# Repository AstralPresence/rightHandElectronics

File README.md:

This repo contains the code on the ESP8266 and pcb designs for each unit.

Currently housing following units:

1) Switch Board Unit

2) Single switch Unit

3) Door unit

4) Safety Unit

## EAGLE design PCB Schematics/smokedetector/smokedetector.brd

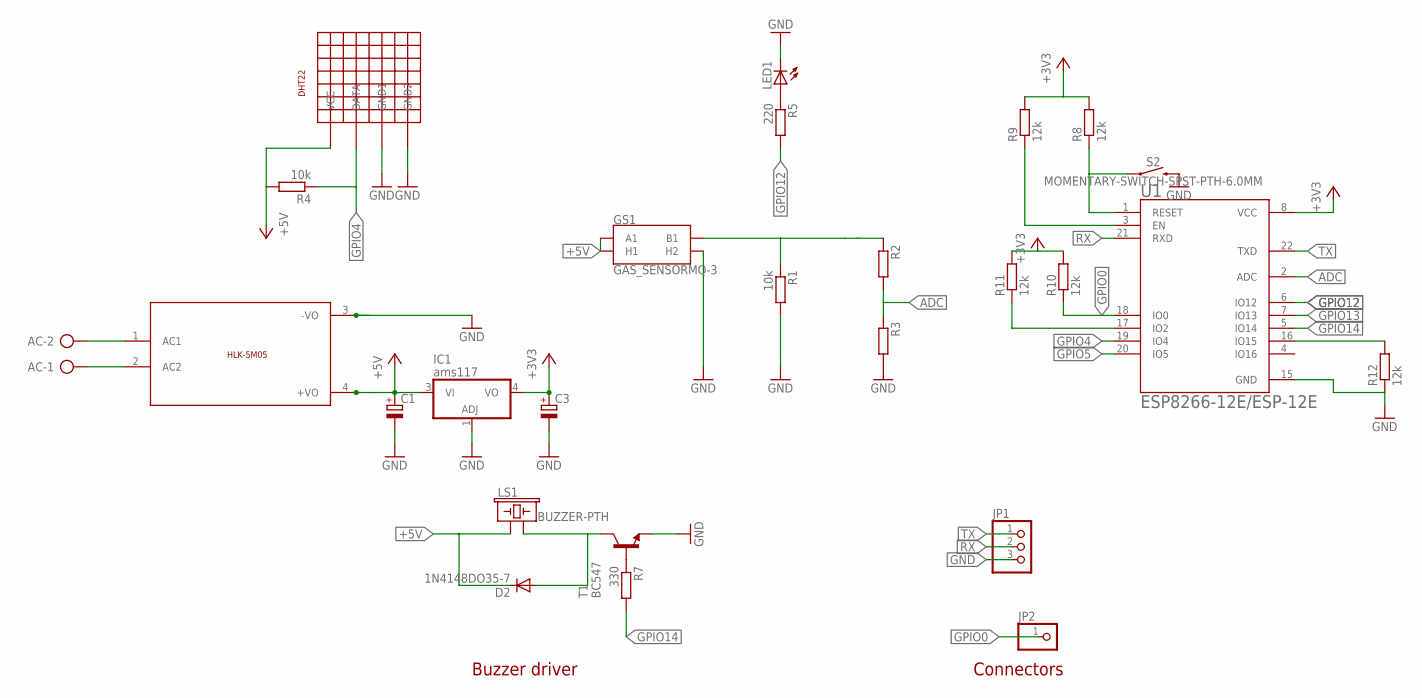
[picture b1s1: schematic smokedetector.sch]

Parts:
AC: AK500/2-H
C1, C3: CPOL-EUE2.5-6; E2,5-6
D2: 1N4148DO35-7; DO35-7
DHT22: DHT22
GS1: GAS_SENSORMQ-3; GAS_SENSOR
IC1: ams117; SOT223
JP1: PINHD-1X3CB; 1X03-CLEANBIG
JP2: PINHD-1X1CB; 1X01-CLEANBIG
LED1: LED5MM
LS1: BUZZER-PTH; BUZZER-12MM
R1, R4: 10k; 0204V
R2, R3: R-EU_0204/2V; 0204V
R5: 220; 0204V
R7: 330; 0204V
R8, R9, R10, R11, R12: 12k; 0204V
S2: MOMENTARY-SWITCH-SPST-PTH-6.0MM; TACTILE_SWITCH_PTH_6.0MM_KIT
T1: BC547; TO92
U1: ESP8266-12E/ESP-12E; XCVR_ESP8266-12E/ESP-12E
U$2: HLK-5M05

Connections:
+3V3: C3.+, IC1.4 (VO), R8.2, R9.2, R10.2, R11.2, U1.8 (VCC)
+5V: C1.+, D2.C, DHT22.P$1 (VCC), GS1.A1, GS1.HA (H1), IC1.3 (VI), LS1.+ (1), R4.2, U$2.4 (+VO)
ADC: R2.2, R3.1, U1.2 (ADC)
GND: C1.-, C3.-, DHT22.P$3 (GND1), DHT22.P$4 (GND2), GS1.HB (H2), IC1.1 (ADJ), JP1.3, LED1.K (C), R1.2, R3.2, R12.1, S2.3 (2), T1.1 (E), U1.15 (GND), U$2.3 (-VO)
GPIO0: JP2.1, R10.1, U1.18 (IO0)
GPIO4: DHT22.P$2 (DATA), R4.1, U1.19 (IO4)
GPIO5: U1.20 (IO5)
GPIO12: R5.2, U1.6 (IO12)
GPIO13: U1.7 (IO13)
GPIO14: R7.2, U1.5 (IO14)
unnamed: R7.1, T1.2 (B)
unnamed: GS1.B1, R1.1, R2.1
unnamed: R8.1, S2.1, U1.1 (RESET)
unnamed: AC.1, U$2.2 (AC2)
unnamed: AC.2, U$2.1 (AC1)
unnamed: D2.A, LS1.- (2), T1.3 (C)
unnamed: R9.1, U1.3 (EN)
unnamed: LED1.A, R5.1
unnamed: R11.1, U1.17 (IO2)
unnamed: R12.2, U1.16 (IO15)
RX: JP1.2, U1.21 (RXD)
TX: JP1.1, U1.22 (TXD)

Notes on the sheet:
Buzzer driver
Connectors

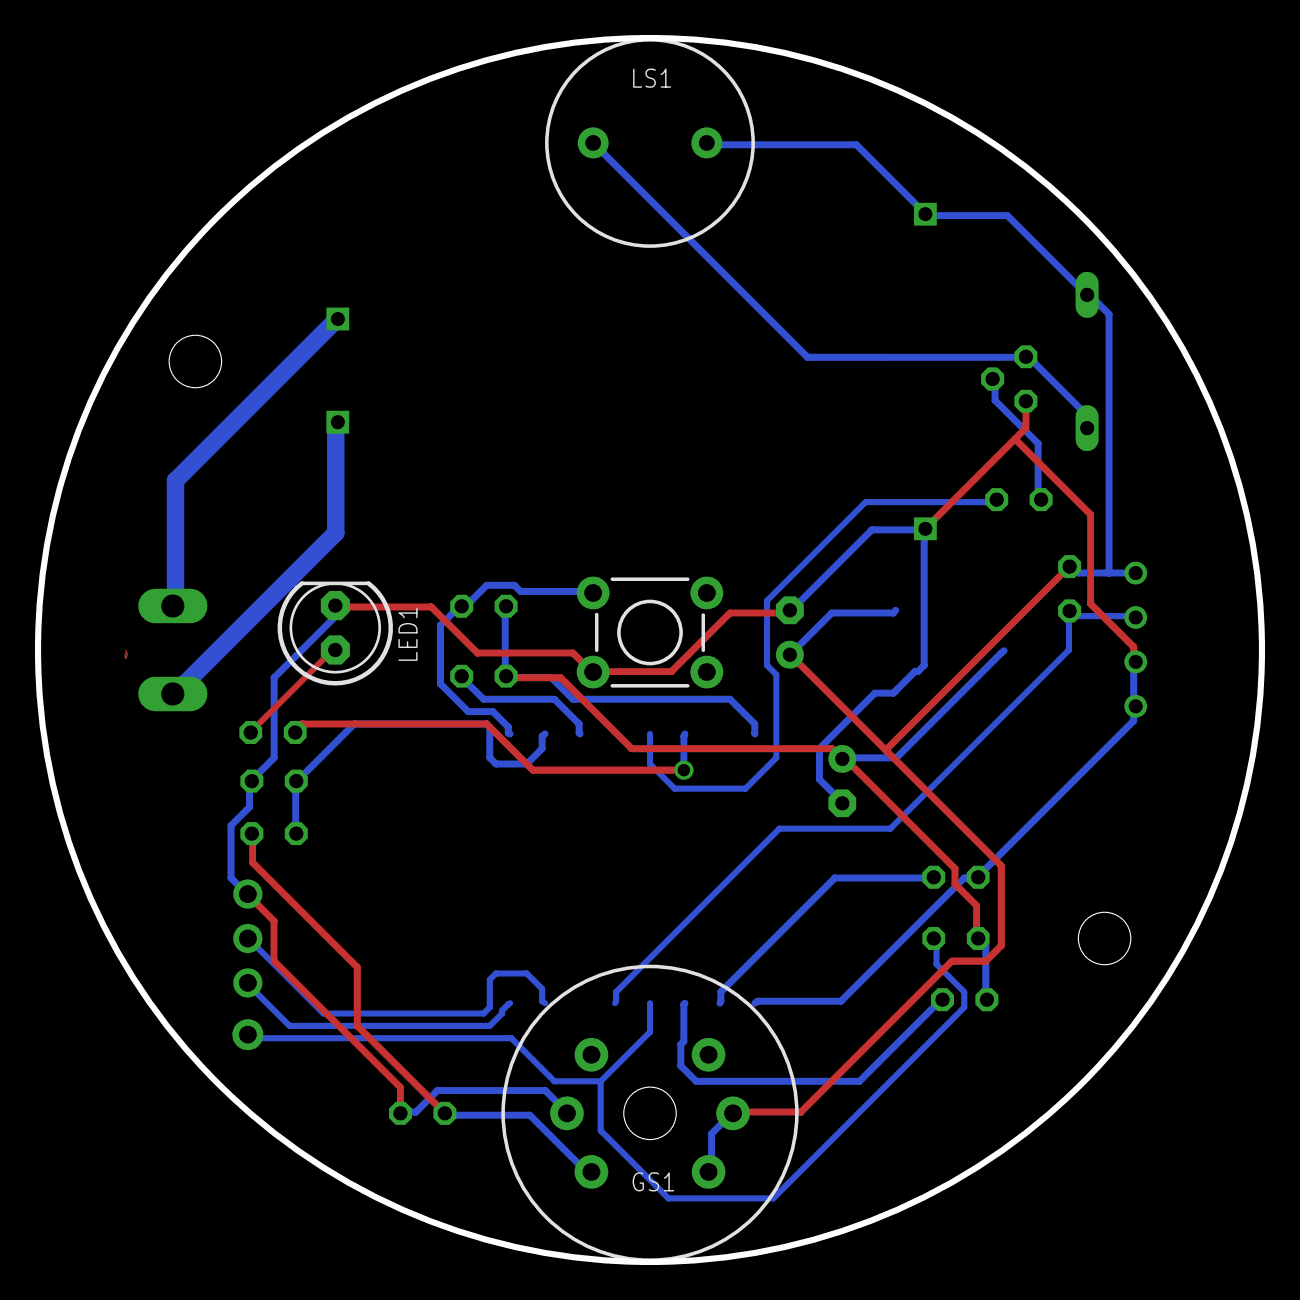
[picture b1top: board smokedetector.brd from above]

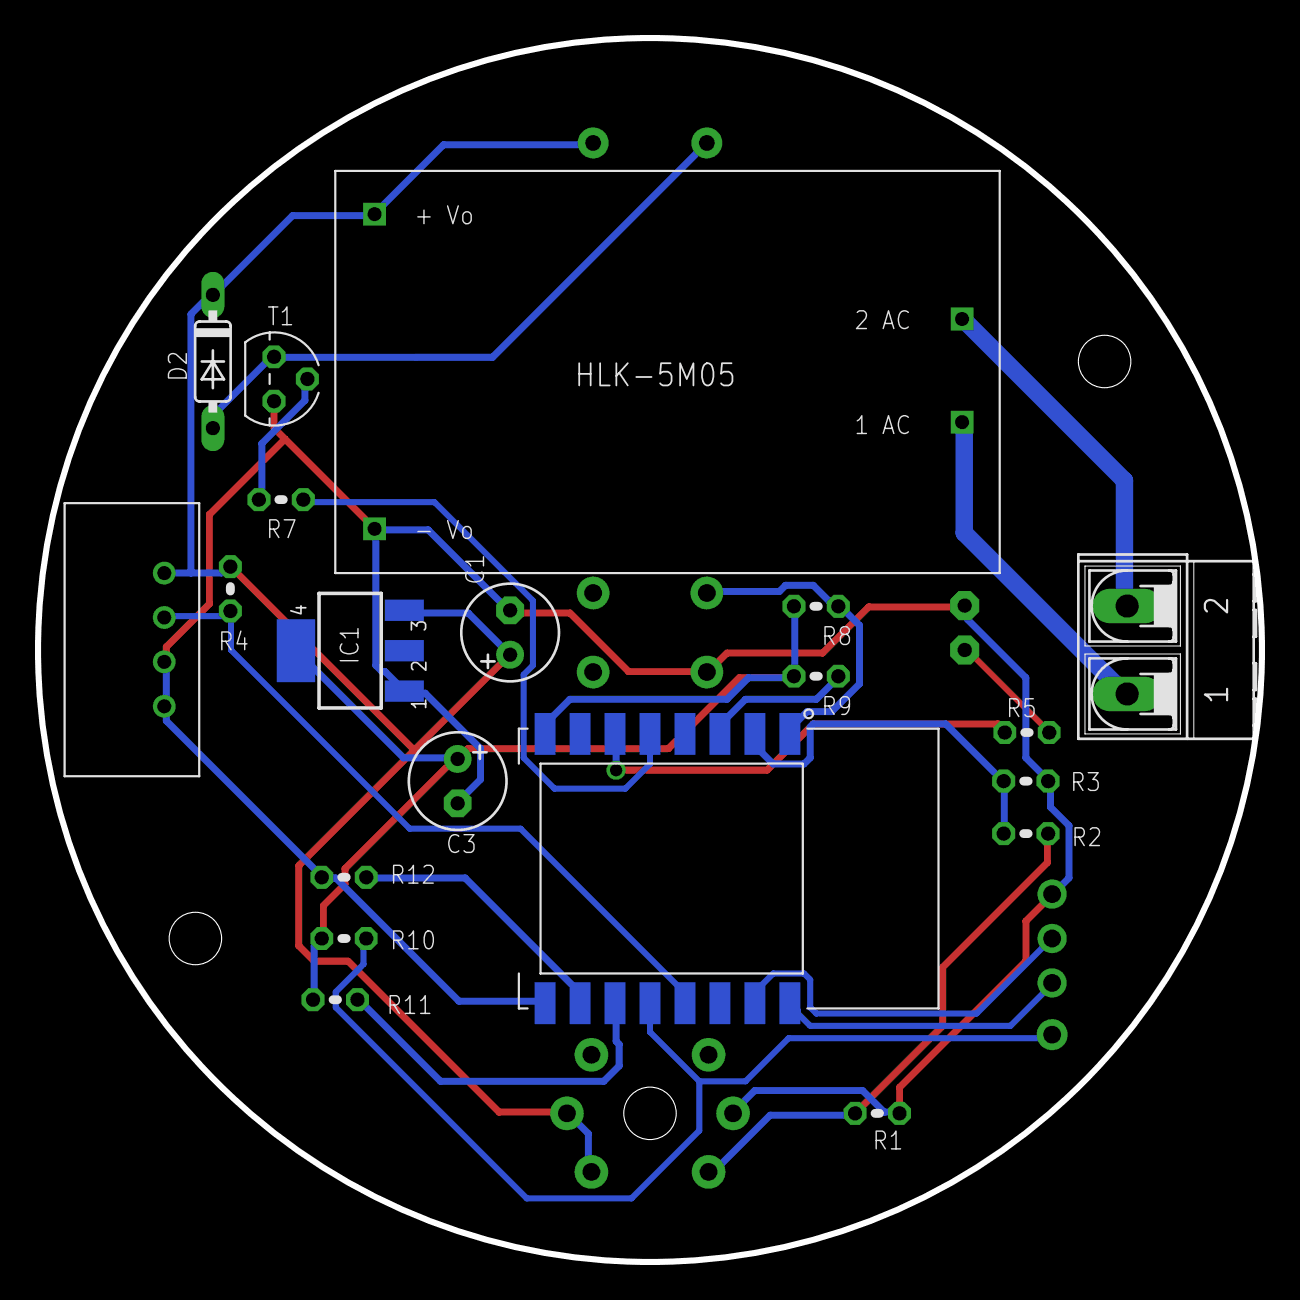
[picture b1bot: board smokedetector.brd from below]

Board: 2 copper layers, 70.0 x 70.0 mm, 26 parts (22 on the bottom side), 20 nets.

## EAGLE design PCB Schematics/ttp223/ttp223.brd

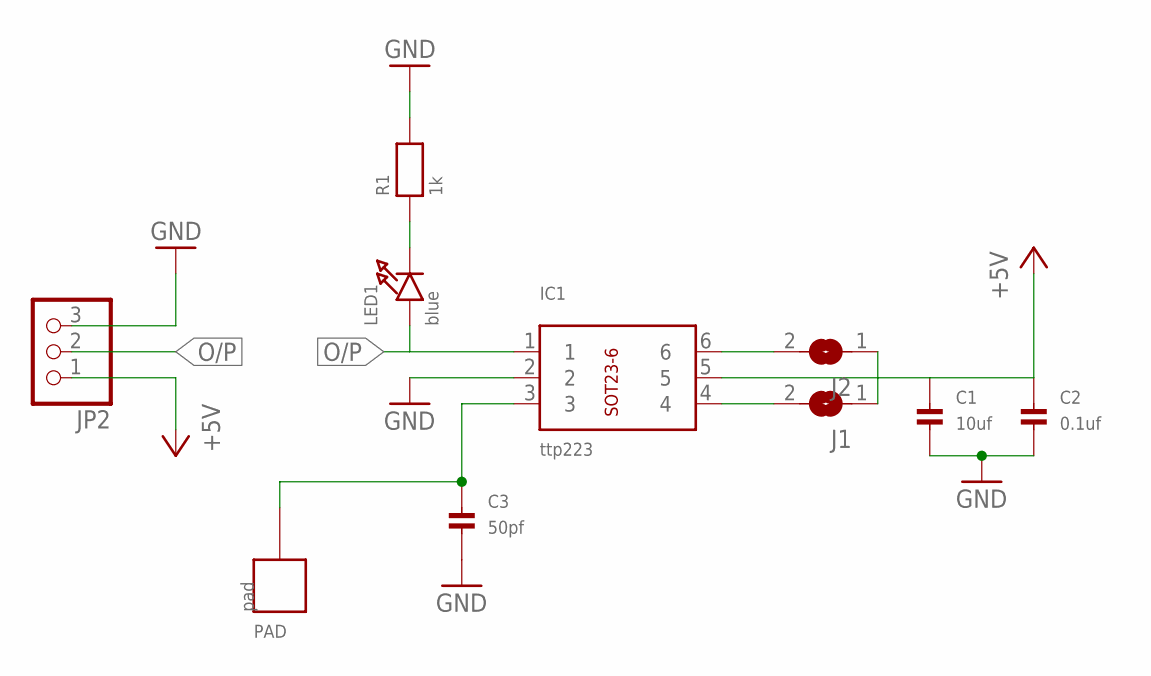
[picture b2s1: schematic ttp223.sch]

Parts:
C1: 10uf; 0805
C2: 0.1uf; 0805
C3: 50pf; 0805
IC1: ttp223; BREAKOUT_SOT23-6
J1, J2: SOLDERJUMPERREFLOW; SOLDERJUMPER_REFLOW
JP2: HEADER-1X3ROUND; 1X03_ROUND
LED1: blue; CHIPLED_0805
PAD: pad; CAP_TOUCHPAD
R1: 1k; 0805

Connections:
+5V: C1.1, C2.1, IC1.5, J1.1, J2.1, JP2.1
GND: C1.2, C2.2, C3.2, IC1.2, JP2.3, R1.2
unnamed: LED1.C, R1.1
unnamed: C3.1, IC1.3, PAD.P$1
unnamed: IC1.6, J2.2
unnamed: IC1.4, J1.2
O/P: IC1.1, JP2.2, LED1.A

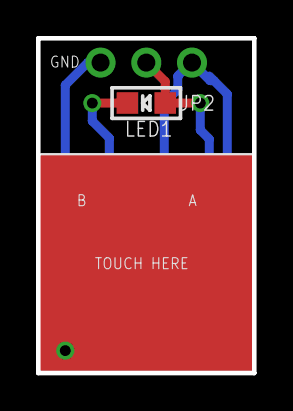
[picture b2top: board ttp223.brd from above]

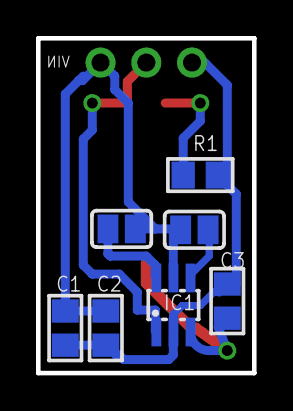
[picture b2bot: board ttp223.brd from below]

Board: 2 copper layers, 12.0 x 18.6 mm, 10 parts (7 on the bottom side), 7 nets.

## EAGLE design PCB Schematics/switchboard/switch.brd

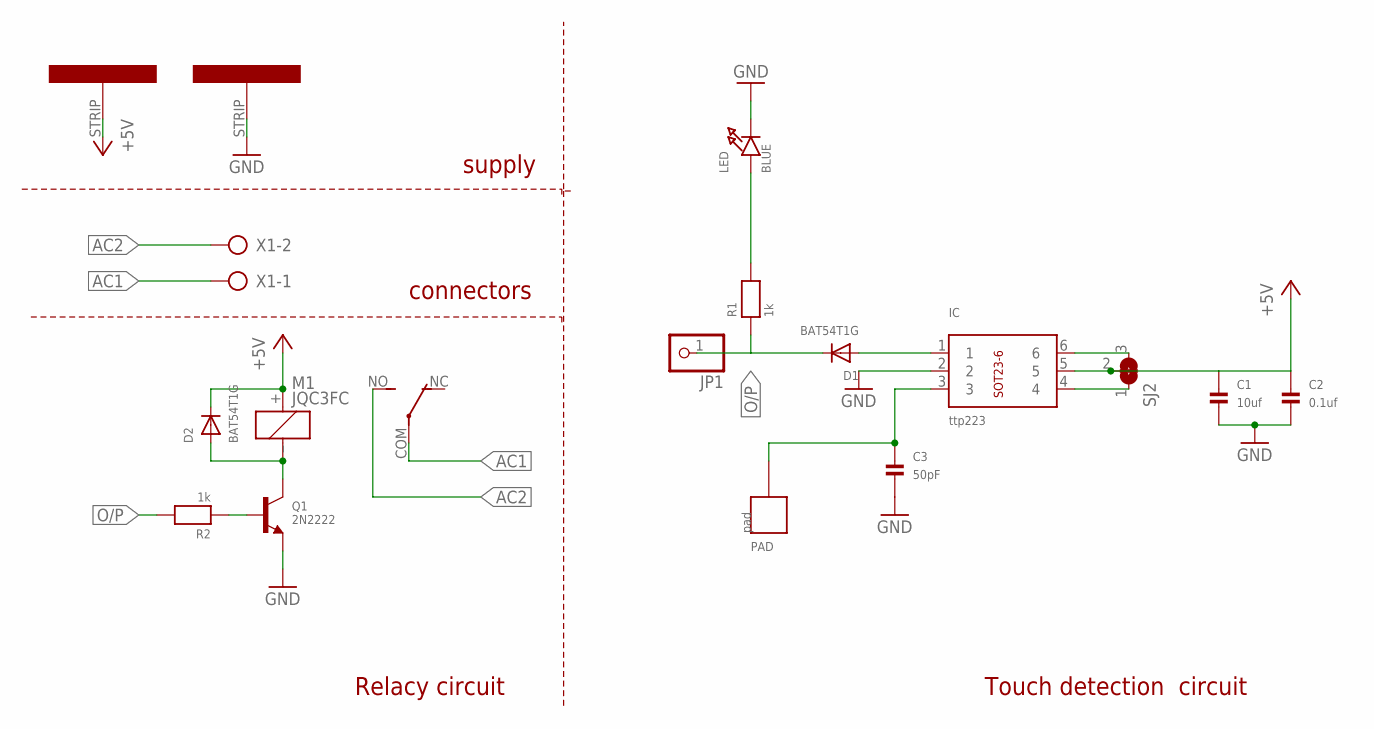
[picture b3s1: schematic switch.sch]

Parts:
C1: 10uf; 0805
C2: 0.1uf; 0805
C3: 50pF; 0805
D1, D2: BAT54T1G; SOD-123
IC: ttp223; BREAKOUT_SOT23-6
JP1: HEADER-1X12MM; 1X01_2MM
LED: BLUE; CHIPLED_0805
M1: JQC3FC
PAD: pad; CAP_TOUCHPAD
Q1: 2N2222; SOT23-W
R1, R2: 1k; 0805
RAIL1: RAIL1; STRIP
RAIL2: RAIL2; STRIP
SJ2: SOLDERJUMPER_2WAY0603; SOLDERJUMPER_2WAY_OPEN_0603
X1: AK500/2-H

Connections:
+5V: C1.1, C2.1, D2.C, IC.5, M1.+, RAIL1.STRIP, SJ2.2
AC1: M1.COM, X1.1
AC2: M1.NO, X1.2
GND: C1.2, C2.2, C3.2, IC.2, LED.C, Q1.2 (E), RAIL2.STRIP
unnamed: LED.A, R1.2
unnamed: D1.A, IC.1
unnamed: C3.1, IC.3, PAD.P$1
unnamed: D2.A, M1._ (-), Q1.3 (C)
unnamed: IC.6, SJ2.3
unnamed: IC.4, SJ2.1
unnamed: Q1.1 (B), R2.1
O/P: D1.C, JP1.1, R1.1, R2.2

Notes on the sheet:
supply
connectors
Relacy circuit
Touch detection circuit

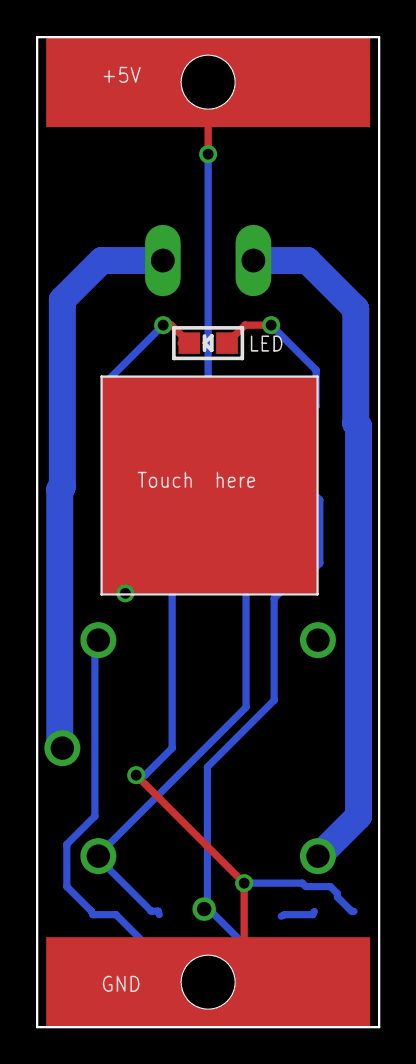
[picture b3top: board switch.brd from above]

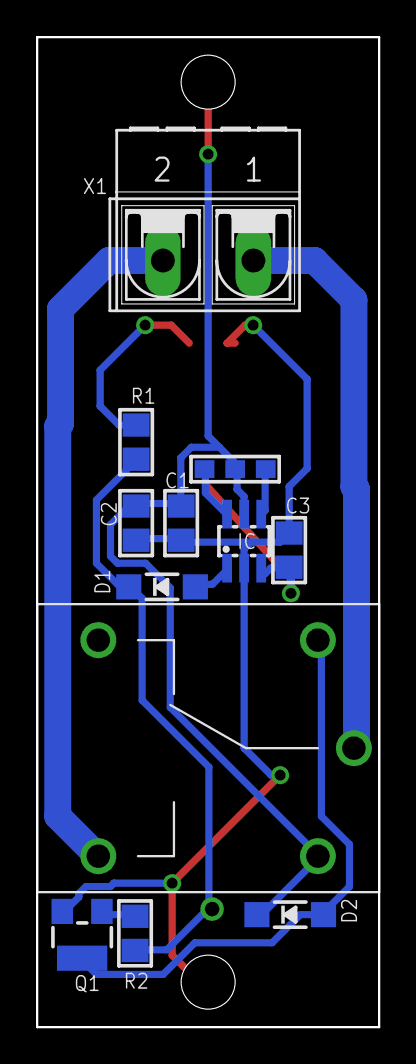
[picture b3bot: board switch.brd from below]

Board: 2 copper layers, 19.0 x 55.0 mm, 17 parts (13 on the bottom side), 12 nets.

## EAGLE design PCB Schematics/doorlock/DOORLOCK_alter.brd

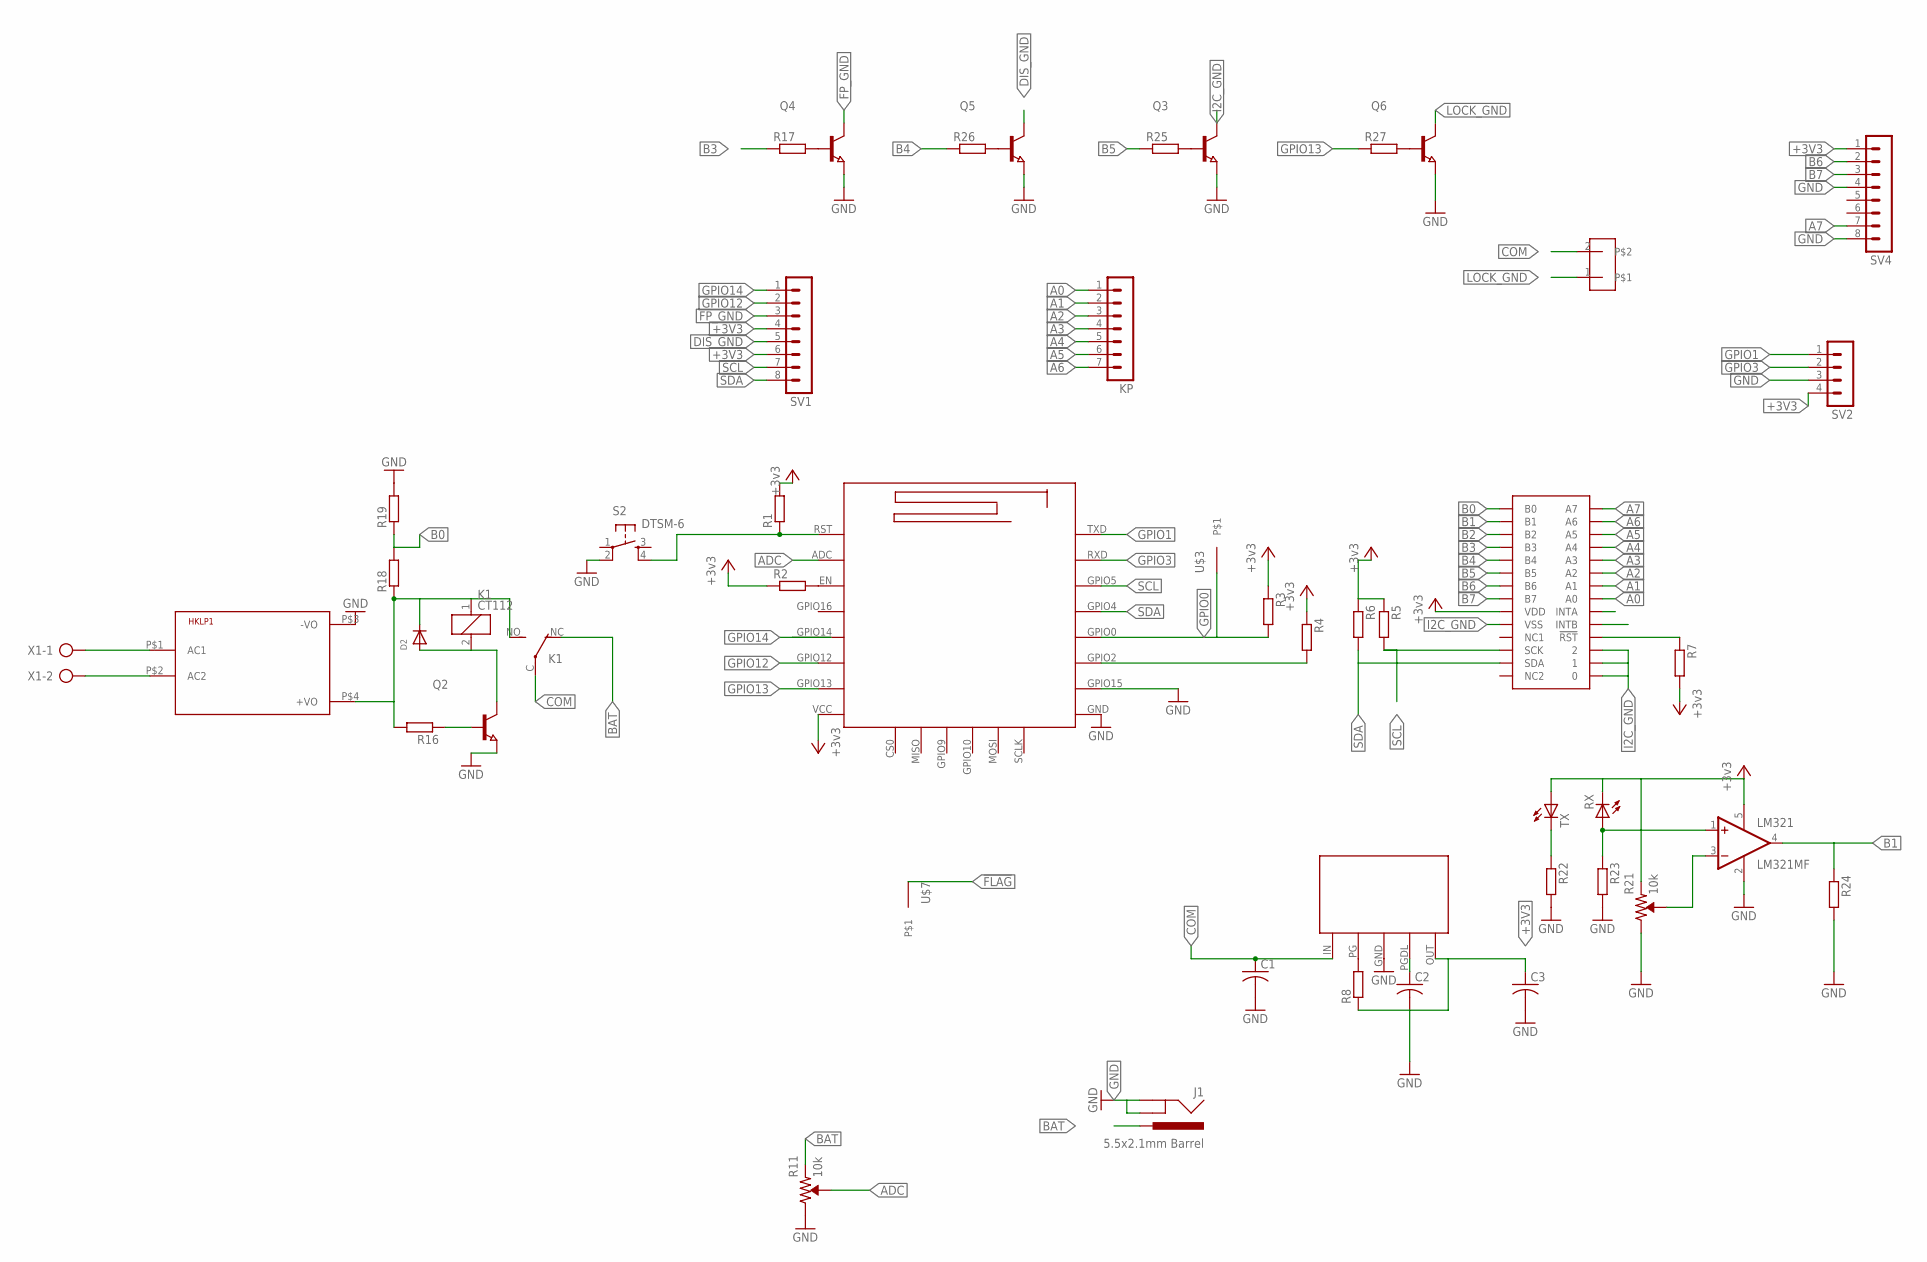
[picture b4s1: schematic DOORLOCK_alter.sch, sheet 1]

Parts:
C1, C2, C3: C-USC1206; C1206
D2: DIODESOD-123; SOD-123
HKLP1: HKLPM01
J1: 5.5x2.1mm Barrel; POWER_JACK_SMD
K1: CT112; CT-SLIM
KP: MA07-1
LM321: LM321MF; SOT23-5
MP2014: MP2014
Q2, Q3, Q4, Q5, Q6: NPN-TRANSISTOR_SOT89; SOT89
R1, R2, R3, R4, R5, R6, R7, R8, R16, R17, R18, R19, R22, R23, R24, R25, R26, R27: R-EU_0204/2V; 0204V
R11, R21: 10k; TRIMPOT-SMD-TC33X
RX: LED5MM
S2: DTSM-6
SV1, SV4: MA08-1
SV2: MA04-1
TX: LED5MM
U$1: ESP12E; ESP-12E
U$2: MCF23017; MAX23017
U$3, U$7: M1
U$4: MALE2PIN
X1: AK500/2-H

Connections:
!FLAG: U$7.P$1; also elsewhere on the board
+3V3: C3.1, LM321.5 (V+), MP2014.OUT, R1.2, R2.1, R3.1, R4.1, R5.1, R6.1, R7.2, R8.1, R21.3 (CCW), RX.K (C), SV1.4, SV1.6, SV2.4, SV4.1, TX.A, U$1.VCC, U$2.P$9 (VDD)
+12V: D2.C, HKLP1.P$4 (+VO), K1.1, K1.NO (S), R16.2, R18.1; also elsewhere on the board
A0: KP.1, U$2.P$21 (A0)
A1: KP.2, U$2.P$22 (A1)
A2: KP.3, U$2.P$23 (A2)
A3: KP.4, U$2.P$24 (A3)
A4: KP.5, U$2.P$25 (A4)
A5: KP.6, U$2.P$26 (A5)
A6: KP.7, U$2.P$27 (A6)
A7: SV4.7, U$2.P$28 (A7)
ADC: R11.2 (WIPER), U$1.ADC; also elsewhere on the board
B0: R18.2, R19.1, U$2.P$1 (B0)
B1: LM321.4 (OUT), R24.1, U$2.P$2 (B1)
B2: U$2.P$3 (B2); also elsewhere on the board
B3: R17.1, U$2.P$4 (B3)
B4: R26.1, U$2.P$5 (B4)
B5: R25.1, U$2.P$6 (B5)
B6: SV4.2, U$2.P$7 (B6)
B7: SV4.3, U$2.P$8 (B7)
BAT: J1.VIN0 (PWR), K1.NC (O), R11.3 (CCW); also elsewhere on the board
COM: C1.1, K1.C, MP2014.IN, U$4.2
DIS_GND: Q5.2 (C), SV1.5
FP_GND: Q4.2 (C), SV1.3
GND: C1.2, C2.2, C3.2, HKLP1.P$3 (-VO), J1.GND (GNDBREAK), J1.P$4 (GND), LM321.2 (V-), MP2014.GND, Q2.3 (E), Q3.3 (E), Q4.3 (E), Q5.3 (E), Q6.3 (E), R11.1 (CW), R19.2, R21.1 (CW), R22.2, R23.2, R24.2, S2.2, SV2.3, SV4.4, SV4.8, U$1.GND, U$1.GPIO15; also elsewhere on the board
GPIO0: R3.2, U$1.GPIO0, U$3.P$1
GPIO1: SV2.1, U$1.TXD
GPIO3: SV2.2, U$1.RXD
GPIO12: SV1.2, U$1.GPIO12
GPIO13: R27.1, U$1.GPIO13
GPIO14: SV1.1, U$1.GPIO14
I2C_GND: Q3.2 (C), U$2.P$10 (VSS), U$2.P$15 (0), U$2.P$16 (1), U$2.P$17 (2)
LOCK_GND: Q6.2 (C), U$4.1
unnamed: R1.1, S2.4, U$1.RST
unnamed: R2.2, U$1.EN
unnamed: HKLP1.P$1 (AC1), X1.1
unnamed: R4.2, U$1.GPIO2
unnamed: LM321.3 (-IN), R21.2 (WIPER)
unnamed: Q3.1 (B), R25.2
unnamed: HKLP1.P$2 (AC2), X1.2
unnamed: R7.1, U$2.P$18 (!RST)
unnamed: MP2014.PG, R8.2
unnamed: C2.1, MP2014.PGDL
unnamed: Q2.1 (B), R16.1
unnamed: Q6.1 (B), R27.2
unnamed: D2.A, K1.2, Q2.2 (C)
unnamed: Q4.1 (B), R17.2
unnamed: R22.1, TX.K (C)
unnamed: Q5.1 (B), R26.2
unnamed: LM321.1 (+IN), R23.1, RX.A
SCL: R5.2, SV1.7, U$1.GPIO5, U$2.P$12 (SCK)
SDA: R6.2, SV1.8, U$1.GPIO4, U$2.P$13 (SDA)

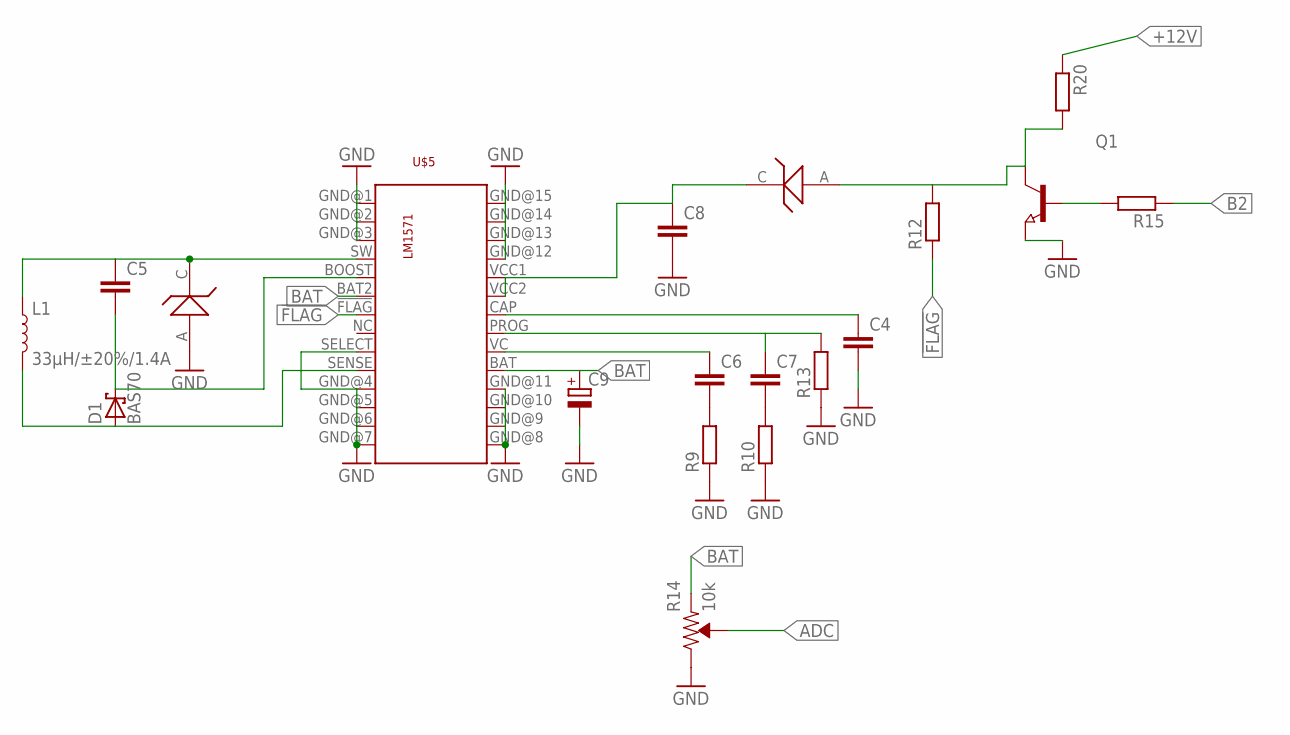
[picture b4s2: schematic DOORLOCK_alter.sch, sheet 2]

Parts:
C4, C5, C6, C7, C8: C-EUC0805; C0805
C9: CPOL-EUCT3216; CT3216
D1: BAS70; SOT23
D3: MBRM120T3
L1: 33µH/±20%/1.4A; SRN6045
Q1: NPN-TRANSISTOR_SOT89; SOT89
R9, R10, R12, R13, R15, R20: R-EU_0204/2V; 0204V
R14: 10k; TRIMPOT-SMD-TC33X
U$5: LM1571; LT1571
U$6: MBRM120T3

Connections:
!FLAG: R12.1, U$5.!FLAG; also elsewhere on the board
+12V: R20.1; also elsewhere on the board
ADC: R14.2 (WIPER); also elsewhere on the board
B2: R15.1; also elsewhere on the board
BAT: C9.+, R14.3 (CCW), U$5.BAT, U$5.BAT2; also elsewhere on the board
GND: C4.2, C8.2, C9.-, Q1.3 (E), R9.1, R10.1, R13.1, R14.1 (CW), U$5.GND@1, U$5.GND@2, U$5.GND@3, U$5.GND@4, U$5.GND@5, U$5.GND@6, U$5.GND@7, U$5.GND@8, U$5.GND@9, U$5.GND@10, U$5.GND@11, U$5.GND@12, U$5.GND@13, U$5.GND@14, U$5.GND@15, U$5.SELECT, U$6.A; also elsewhere on the board
unnamed: Q1.1 (B), R15.2
unnamed: C8.1, D3.C, U$5.VCC1, U$5.VCC2
unnamed: C4.1, U$5.CAP
unnamed: D3.A, Q1.2 (C), R12.2, R20.2
unnamed: D1.1 (A), L1.2, U$5.SENSE
unnamed: C5.1, L1.1, U$5.SW, U$6.C
unnamed: C5.2, D1.3 (C), U$5.BOOST
unnamed: C6.2, R9.2
unnamed: C6.1, U$5.VC
unnamed: C7.2, R10.2
unnamed: C7.1, R13.2, U$5.PROG

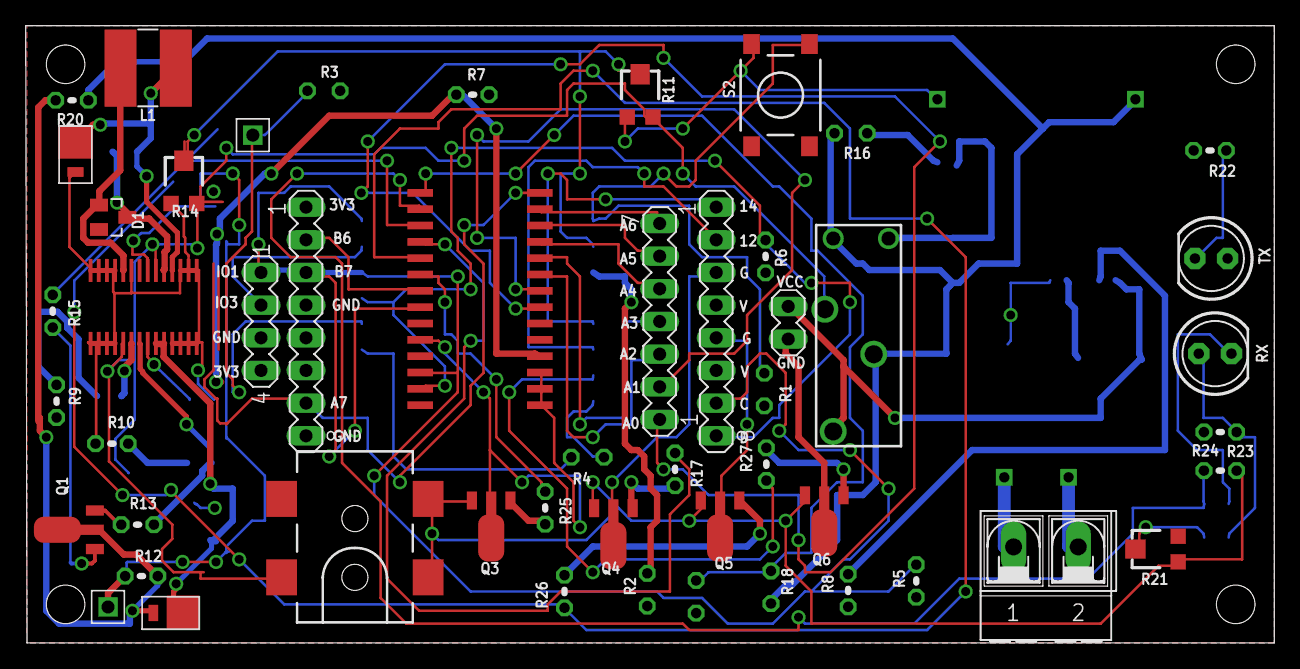
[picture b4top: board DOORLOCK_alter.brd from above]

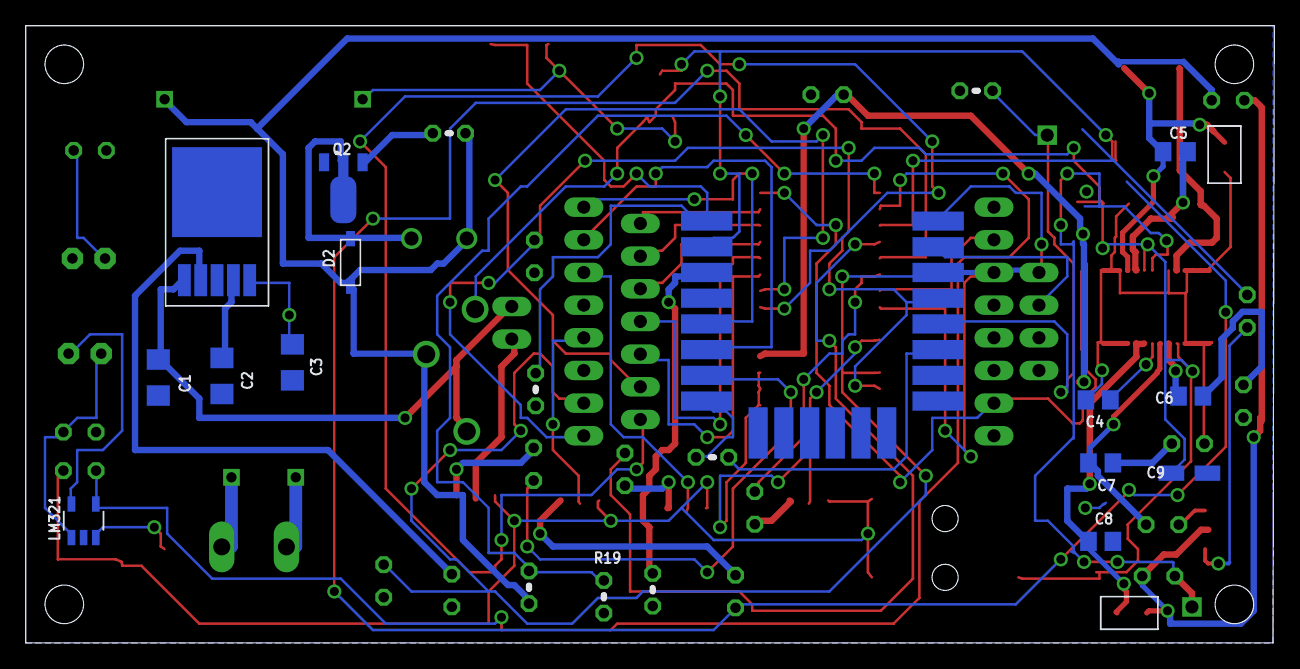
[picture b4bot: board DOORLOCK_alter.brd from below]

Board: 2 copper layers, 97.0 x 47.9 mm, 66 parts (21 on the bottom side), 63 nets.

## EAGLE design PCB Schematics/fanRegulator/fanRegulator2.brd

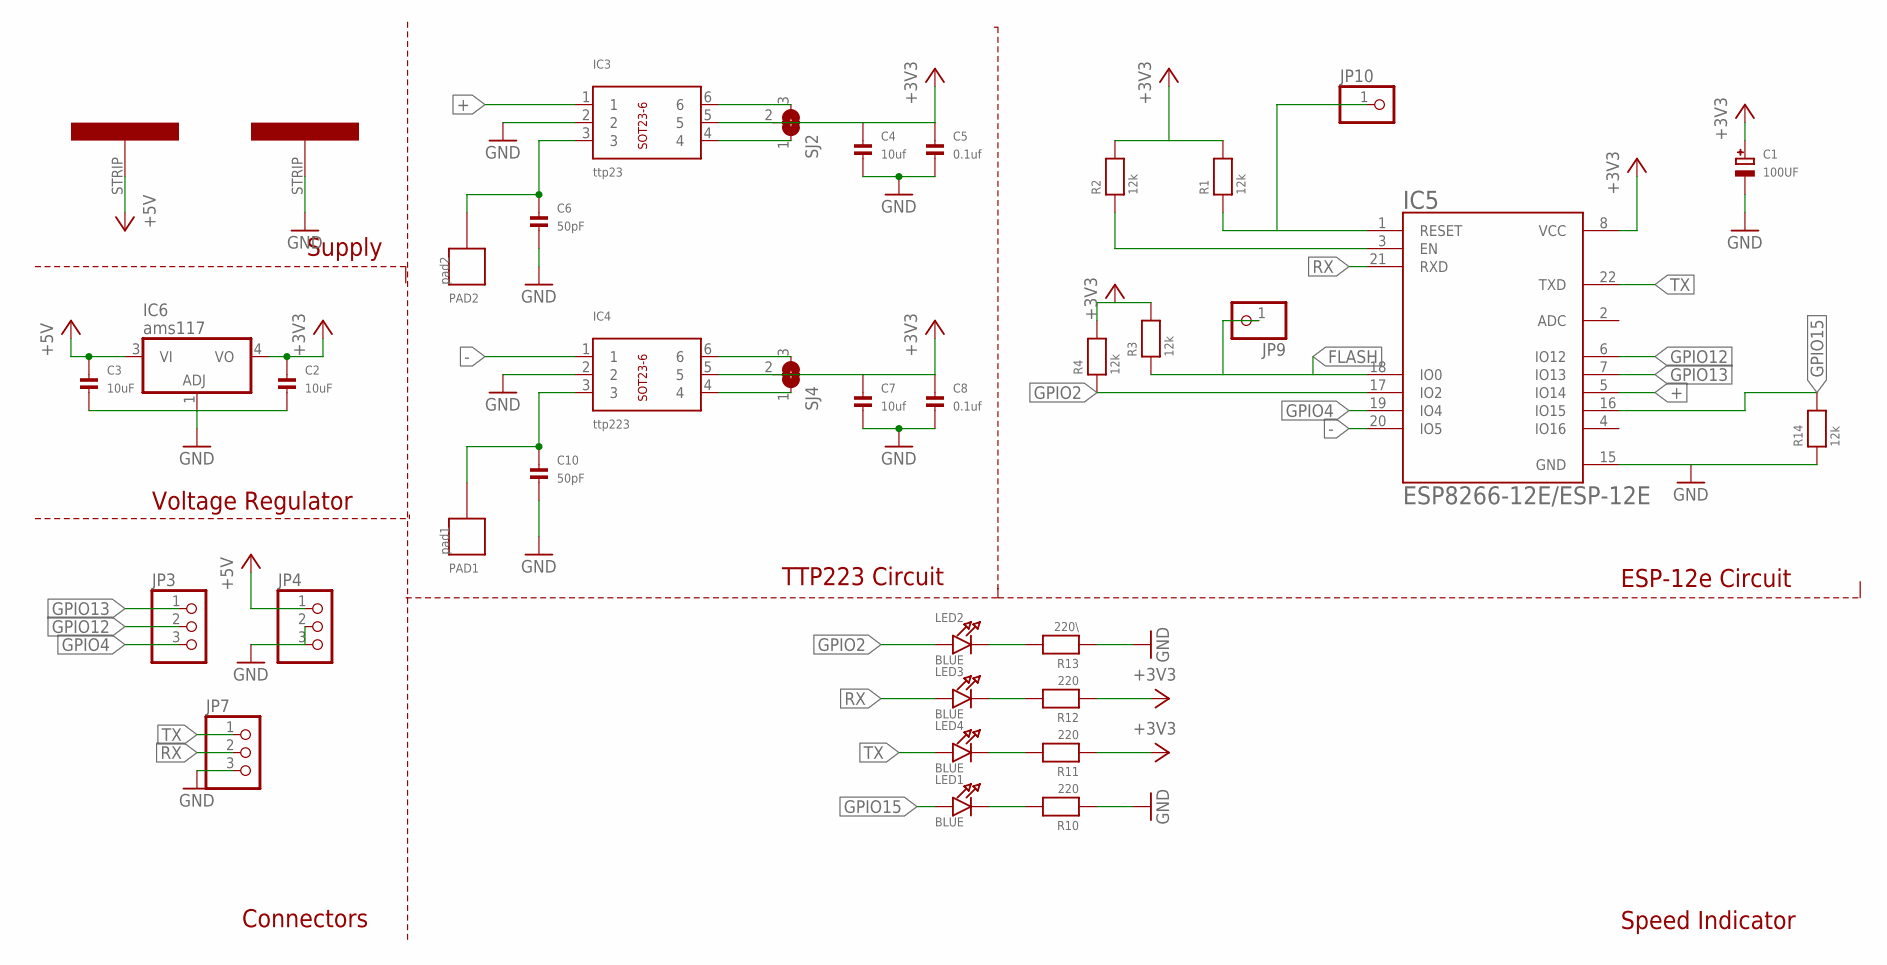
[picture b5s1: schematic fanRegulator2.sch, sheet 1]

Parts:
C1: 100UF; EIA6032-28/C-W
C2, C3: 10uF; 0805
C4, C7: 10uf; 0805
C5, C8: 0.1uf; 0805
C6, C10: 50pF; 0805
IC3: ttp23; BREAKOUT_SOT23-6
IC4: ttp223; BREAKOUT_SOT23-6
IC5: ESP8266-12E/ESP-12E; XCVR_ESP8266-12E/ESP-12E
IC6: ams117; SOT223
JP3, JP4: PINHD-1X3; 1X03
JP7: PINHD-1X3CB; 1X03-CLEANBIG
JP9, JP10: PINHD-1X1; 1X01
LED1, LED2, LED3, LED4: BLUE; CHIPLED_0805
PAD1: pad1; CAP_TOUCHPAD
PAD2: pad2; CAP_TOUCHPAD
R1, R2, R3, R4, R14: 12k; 0805
R10, R11, R12: 220; 0805
R13: 220\; 0805
SJ2, SJ4: SOLDERJUMPER_2WAY0603; SOLDERJUMPER_2WAY_OPEN_0603
U$2, U$3: STRIP

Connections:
+: IC3.1, IC5.5 (IO14)
+3V3: C1.+, C2.1, C4.1, C5.1, C7.1, C8.1, IC3.5, IC4.5, IC5.8 (VCC), IC6.4 (VO), R1.2, R2.2, R3.2, R4.2, R11.1, R12.1, SJ2.2, SJ4.2
+5V: C3.1, IC6.3 (VI), JP4.1, U$2.STRIP
-: IC4.1, IC5.20 (IO5)
FLASH: IC5.18 (IO0), JP9.1, R3.1
GND: C1.-, C2.2, C3.2, C4.2, C5.2, C6.2, C7.2, C8.2, C10.2, IC3.2, IC4.2, IC5.15 (GND), IC6.1 (ADJ), JP4.2, JP4.3, JP7.3, R10.1, R13.1, R14.1, U$3.STRIP
GPIO2: IC5.17 (IO2), LED2.A, R4.1
GPIO4: IC5.19 (IO4), JP3.3
GPIO12: IC5.6 (IO12), JP3.2
GPIO13: IC5.7 (IO13), JP3.1
GPIO15: IC5.16 (IO15), LED1.A, R14.2
unnamed: C6.1, IC3.3, PAD2.P$1
unnamed: IC5.1 (RESET), JP10.1, R1.1
unnamed: IC5.3 (EN), R2.1
unnamed: IC3.6, SJ2.3
unnamed: IC3.4, SJ2.1
unnamed: C10.1, IC4.3, PAD1.P$1
unnamed: IC4.6, SJ4.3
unnamed: IC4.4, SJ4.1
unnamed: LED1.C, R10.2
unnamed: LED4.C, R11.2
unnamed: LED3.C, R12.2
unnamed: LED2.C, R13.2
RX: IC5.21 (RXD), JP7.2, LED3.A
TX: IC5.22 (TXD), JP7.1, LED4.A

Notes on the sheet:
Supply
Voltage Regulator
Connectors
Speed Indicator
ESP-12e Circuit
TTP223 Circuit

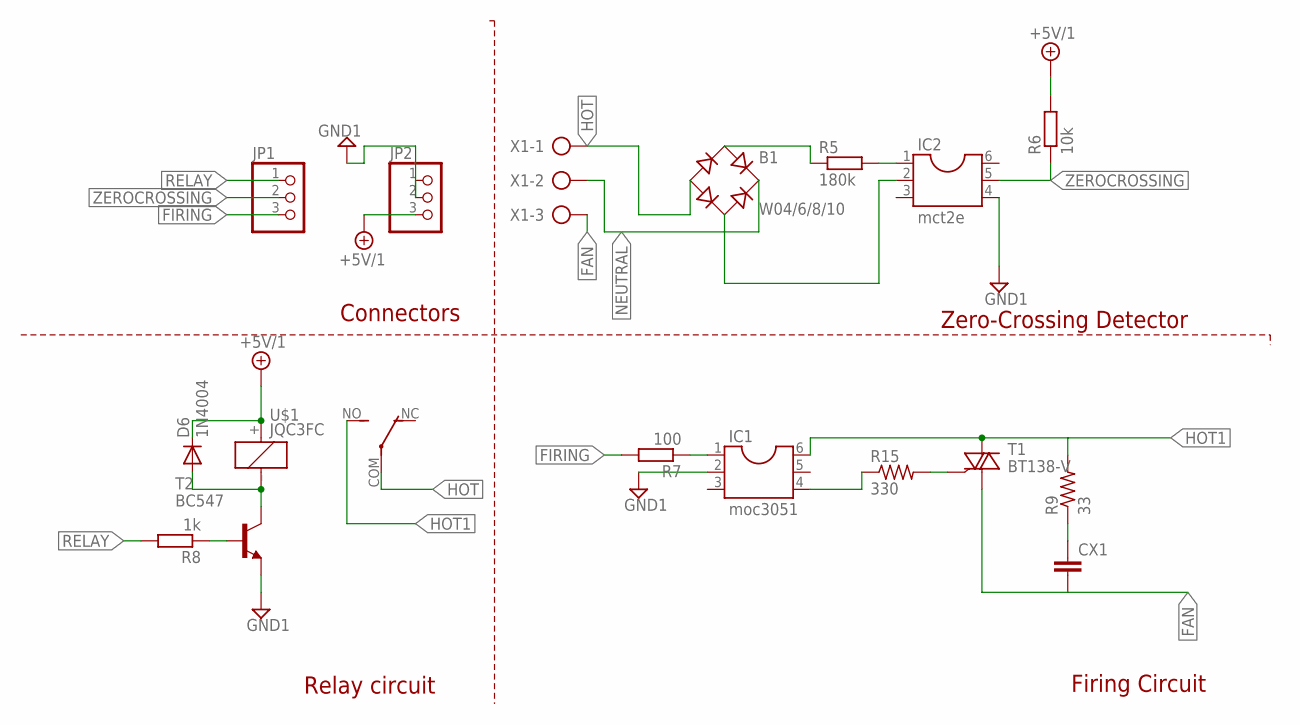
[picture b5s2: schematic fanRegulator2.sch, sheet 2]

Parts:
B1: W04/6/8/10; RB1A
CX1: C-EU050-024X044; C050-024X044
D6: 1N4004; DO41-10
IC1: moc3051; DIL06
IC2: mct2e; DIL06
JP1, JP2: PINHD-1X3; 1X03
R5: 180k; 0309V
R6: 10k; 0204V
R7: 100; 0204V
R8: 1k; 0204V
R9: 33; 0411V
R15: 330; 0207/2V
T1: BT138-V; TO220BV
T2: BC547; TO92
U$1: JQC3FC
X1: AK500/3-H

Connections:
+5V/1: D6.C, JP2.3, R6.2, U$1.+
FAN: CX1.2, T1.T1 (A1), X1.3
FIRING: JP1.3, R7.2
GND1: IC1.2, IC2.4, JP2.1, JP2.2, T2.1 (E)
HOT: B1.-, U$1.COM, X1.1
HOT1: IC1.6, R9.2, T1.T2 (A2), U$1.NO
unnamed: B1.AC1, R5.1
unnamed: B1.AC2, IC2.2
unnamed: IC2.1, R5.2
unnamed: IC1.1, R7.1
unnamed: IC1.4, R15.1
unnamed: R15.2, T1.G
unnamed: CX1.1, R9.1
unnamed: D6.A, T2.3 (C), U$1._ (-)
unnamed: R8.1, T2.2 (B)
NEUTRAL: B1.+, X1.2
RELAY: JP1.1, R8.2
ZEROCROSSING: IC2.5, JP1.2, R6.1

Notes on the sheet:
Connectors
Relay circuit
Zero-Crossing Detector
Firing Circuit

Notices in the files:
parts and their libraries:
SparkFun-Resistors: Licensing: Creative Commons ShareAlike 4.0 International - https://creativecommons.org/licenses/by-sa/4.0
microbuilder: This work is placed in the public domain, and may be freely used for commercial and non-commercial work with the following conditions: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
